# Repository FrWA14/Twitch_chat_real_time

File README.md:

Toutes les informations concernant ce projet se trouvent dans un PDF à l'intérieur du dossier.

Le projet a pour but d'afficher un chat Twitch en temps réel sur un écran ILI9488.

Il présentera dans l'ordre :
- Un code Python permettant d'afficher le chat Twitch en temps réel.
- Une adaptation du code python en version Arduino pour ESP32 afin d'afficher le chat Twitch en temps réel via le port série.
- Une intégration sur un écran tactile ILI9488 afin d'afficher le chat sur l'écran en temps réel.

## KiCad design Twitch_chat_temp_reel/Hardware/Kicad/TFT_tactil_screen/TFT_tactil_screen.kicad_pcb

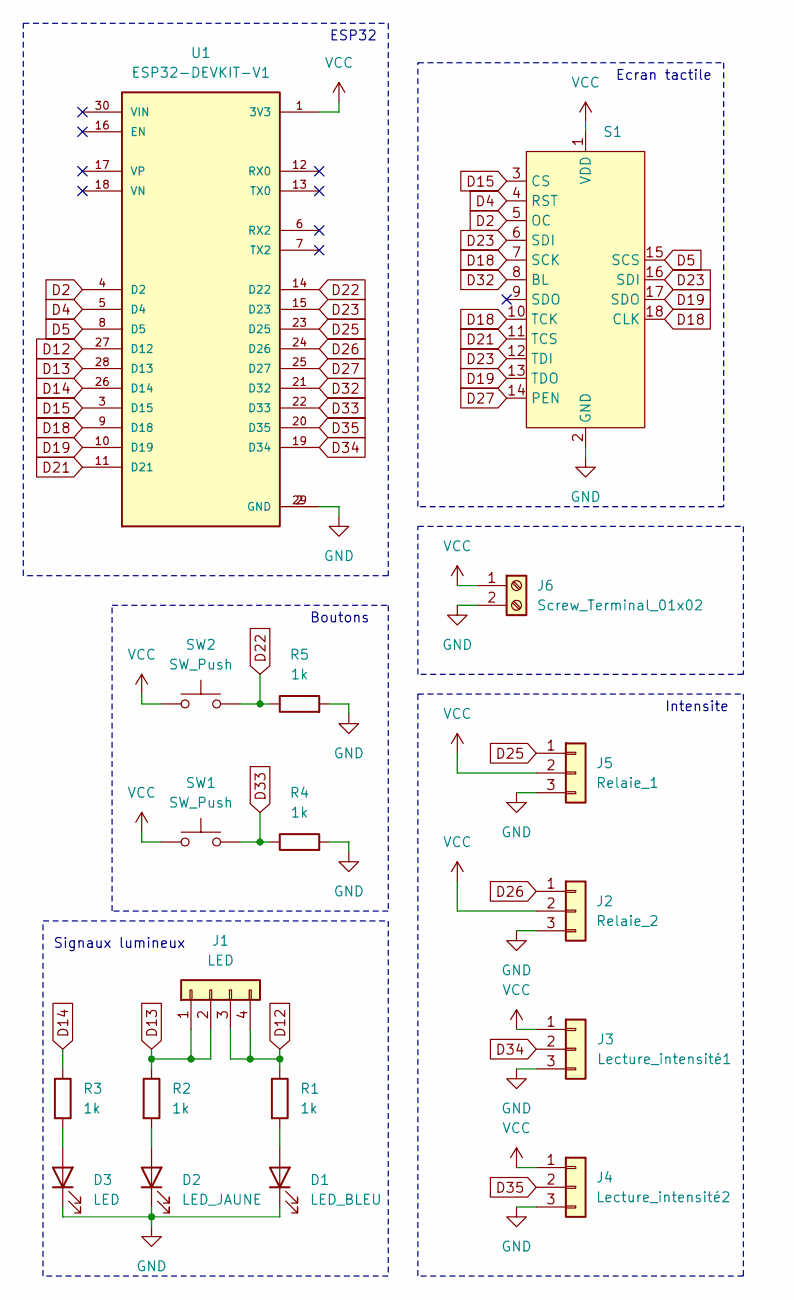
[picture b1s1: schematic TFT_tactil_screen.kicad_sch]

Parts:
D1: LED_BLEU; LED_D3.0mm
D2: LED_JAUNE; LED_D3.0mm
D3: LED; LED_D3.0mm
J1: LED; PinHeader_1x04_P2.54mm_Vertical
J2: Relaie_2; PinSocket_1x03_P2.54mm_Vertical
J3: Lecture_intensité1; PinSocket_1x03_P2.54mm_Vertical
J4: Lecture_intensité2; PinSocket_1x03_P2.54mm_Vertical
J5: Relaie_1; PinSocket_1x03_P2.54mm_Vertical
J6: Screw_Terminal_01x02; TerminalBlock_Phoenix_MPT-0,5-2-2.54_1x02_P2.54mm_Horizontal
R1, R2, R3, R4, R5: 1k; R_Axial_DIN0207_L6.3mm_D2.5mm_P10.16mm_Horizontal
S1: ILI9488_4inch_touch_screen
SW1, SW2: SW_Push; SW_PUSH-12mm
U1: ESP32-DEVKIT-V1; MODULE_ESP32_DEVKIT_V1; PARTREV N/A

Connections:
D2: S1.5 (OC), U1.4 (D2)
D4: S1.4 (RST), U1.5 (D4)
D5: S1.15 (SCS), U1.8 (D5)
D12: J1.3, J1.4, R1.1, U1.27 (D12)
D13: J1.1, J1.2, R2.1, U1.28 (D13)
D14: R3.1, U1.26 (D14)
D15: S1.3 (CS), U1.3 (D15)
D18: S1.7 (SCK), S1.10 (TCK), S1.18 (CLK), U1.9 (D18)
D19: S1.13 (TDO), S1.17 (SDO), U1.10 (D19)
D21: S1.11 (TCS), U1.11 (D21)
D22: R5.1, SW2.2, U1.14 (D22)
D23: S1.6 (SDI), S1.12 (TDI), S1.16 (SDI), U1.15 (D23)
D25: J5.1, U1.23 (D25)
D26: J2.1, U1.24 (D26)
D27: S1.14 (PEN), U1.25 (D27)
D32: S1.8 (BL), U1.21 (D32)
D33: R4.1, SW1.2, U1.22 (D33)
D34: J3.2, U1.19 (D34)
D35: J4.2, U1.20 (D35)
GND: D1.1 (K), D2.1 (K), D3.1 (K), J2.3, J3.3, J4.3, J5.3, J6.2, R4.2, R5.2, S1.2 (GND), U1.2 (GND), U1.29 (GND)
unnamed: D1.2 (A), R1.2
unnamed: D2.2 (A), R2.2
unnamed: D3.2 (A), R3.2
VCC: J2.2, J3.1, J4.1, J5.2, J6.1, S1.1 (VDD), SW1.1, SW2.1, U1.1 (3V3)

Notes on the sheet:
ESP32
Boutons
Ecran tactile
Intensite
Signaux lumineux

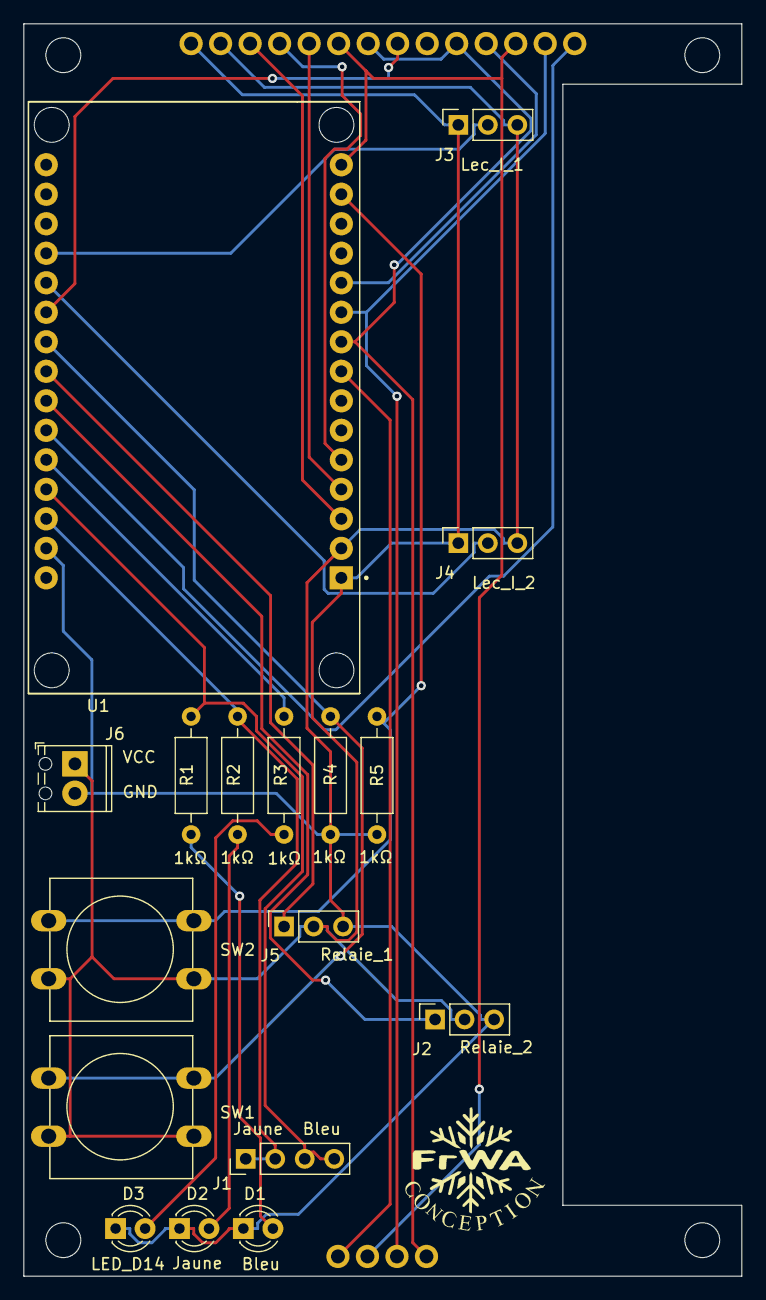
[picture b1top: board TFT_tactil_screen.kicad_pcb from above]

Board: 2 copper layers, 61.8 x 107.8 mm, 18 parts (1 on the bottom side), 24 nets.
